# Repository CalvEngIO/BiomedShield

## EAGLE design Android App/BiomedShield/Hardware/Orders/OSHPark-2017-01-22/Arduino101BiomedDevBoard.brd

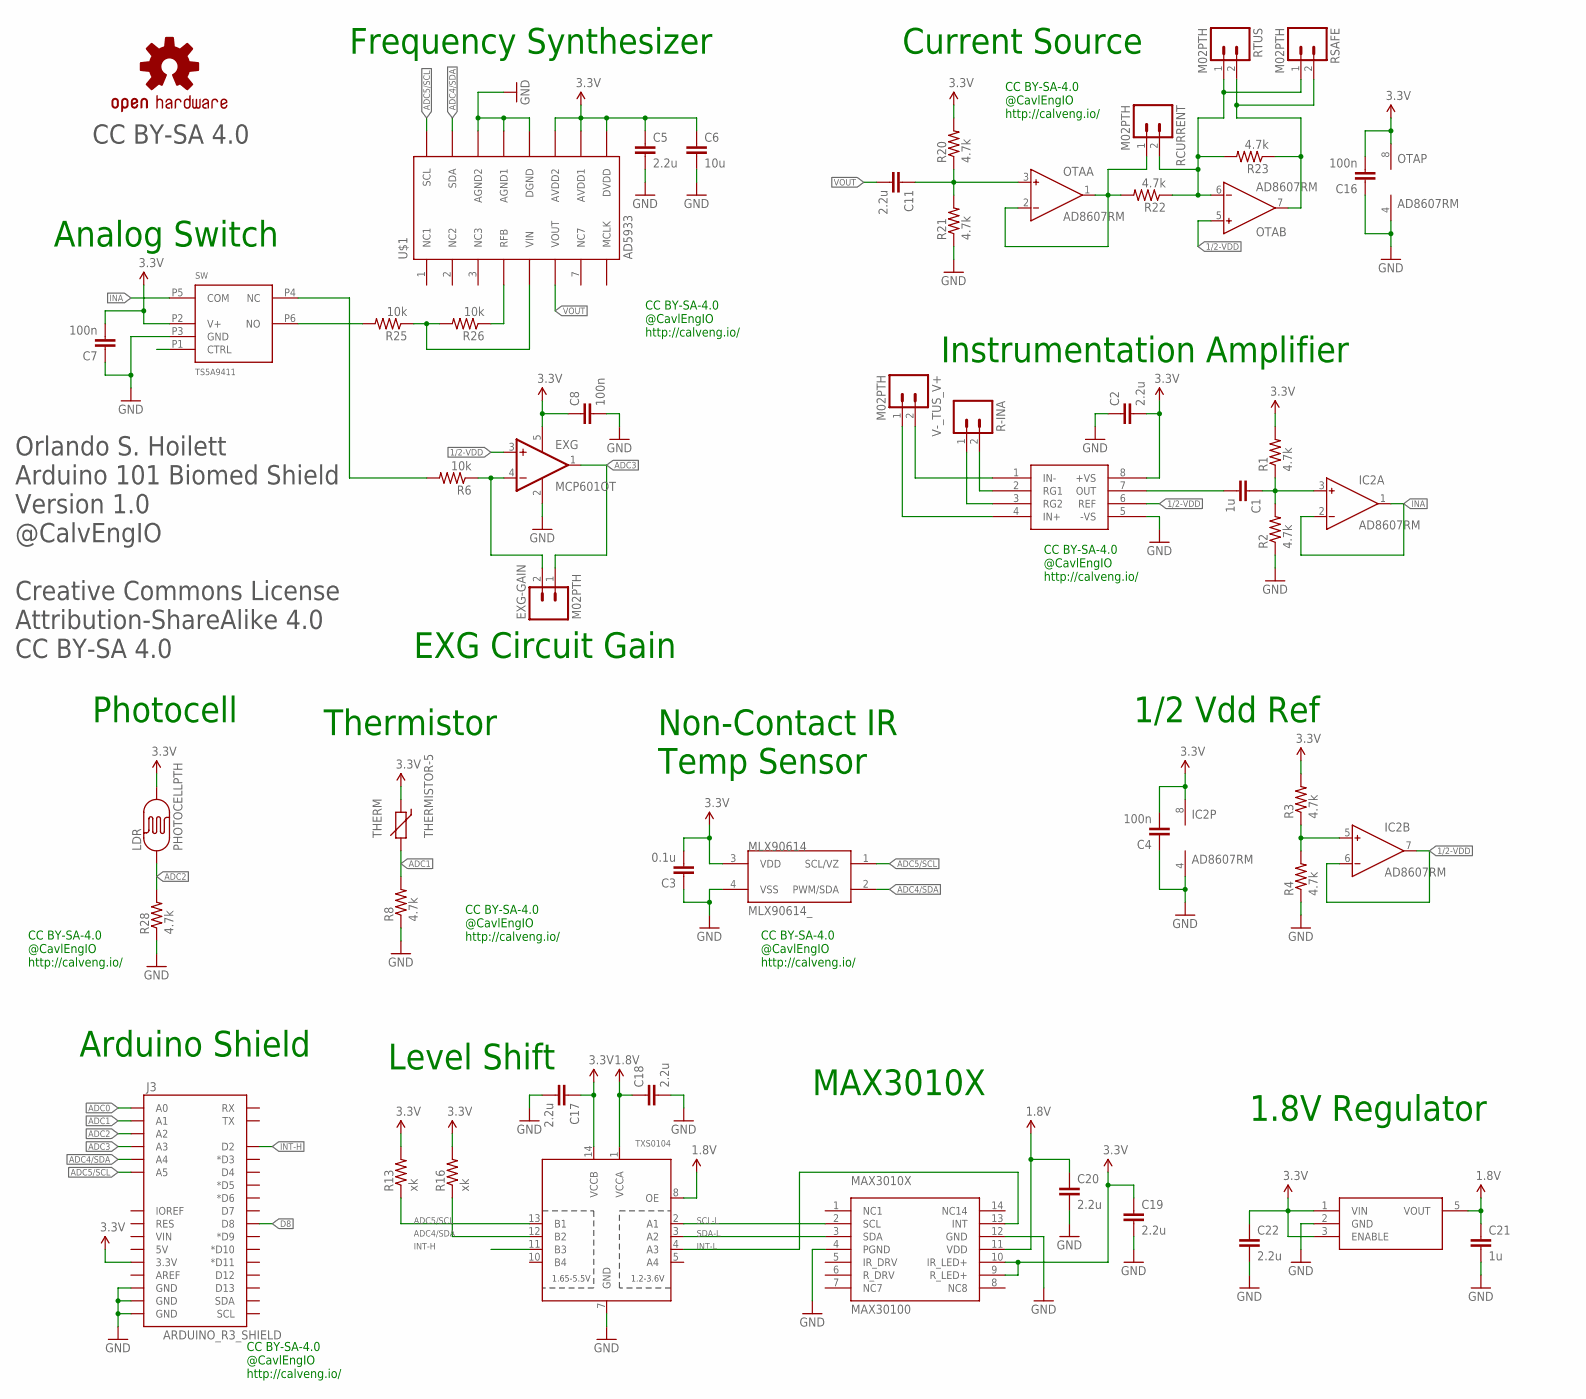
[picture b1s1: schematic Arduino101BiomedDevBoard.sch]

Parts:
1.8V: MIC5504; SOT23-5
C1, C21: 1u; C0402
C2, C5, C11, C17, C18, C19, C20, C22: 2.2u; C0402
C3: 0.1u; C0402
C4, C7, C8, C16: 100n; C0402
C6: 10u; C0805
EXG: MCP601OT; SOT23-5
EXG-GAIN: M02PTH; 1X02
IC2: AD8607RM; MSOP08
INA: AD8220; MSOP08
J3: ARDUINO_R3_SHIELD; UNO_R3_SHIELD
LDR: PHOTOCELLPTH; PHOTOCELL
LOGO3: OSHW-LOGOM; OSHW-LOGO-M
MAX3010X: MAX30100; OESIP14
MLX90614: MLX90614_; TO-39
OTA: AD8607RM; MSOP08
R1, R2, R3, R4, R8, R20, R21, R22, R23, R28: 4.7k; R0402
R6, R25, R26: 10k; R0402
R13, R16: xk; R0402
R-INA: M02PTH; 1X02
RCURRENT: M02PTH; 1X02
RSAFE: M02PTH; 1X02
RTUS: M02PTH; 1X02
SW: TS5A9411; SOT-363
THERM: THERMISTOR-5; R-5
TXS0104: TXB0104PWR; TSSOP14
U$1: AD5933; SSOP-16
V-_TUS_V+: M02PTH; 1X02

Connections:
1.8V: 1.8V.5 (VOUT), C18.1, C20.1, C21.1, MAX3010X.11 (VDD), TXS0104.1 (VCCA), TXS0104.8 (OE)
1/2-VDD: EXG.3 (+IN), IC2.6 (IN-), IC2.7 (OUT), INA.6 (REF), OTA.5 (IN+)
3.3V: 1.8V.1 (VIN), 1.8V.3 (ENABLE), C2.2, C3.2, C4.2, C5.1, C6.1, C7.2, C8.1, C16.2, C17.1, C19.1, C22.1, EXG.5 (V+), IC2.8 (V+), INA.8 (+VS), J3.3.3V, LDR.2, MAX3010X.9 (R_LED+), MAX3010X.10 (IR_LED+), MLX90614.3 (VDD), OTA.8 (V+), R1.2, R3.2, R13.2, R16.2, R20.2, SW.P2 (V+), THERM.1, TXS0104.14 (VCCB), U$1.9 (DVDD), U$1.10 (AVDD1), U$1.11 (AVDD2)
ADC0: J3.A0
ADC1: J3.A1, R8.2, THERM.2
ADC2: J3.A2, LDR.1, R28.2
ADC3: EXG.1 (OUT), EXG-GAIN.1, J3.A3
ADC4/SDA: J3.A4, MLX90614.2 (PWM/SDA), R16.1, TXS0104.12 (B2), U$1.15 (SDA)
ADC5/SCL: J3.A5, MLX90614.1 (SCL/VZ), R13.1, TXS0104.13 (B1), U$1.16 (SCL)
D8: J3.D8, SW.P1 (CTRL)
GND: 1.8V.2 (GND), C2.1, C3.1, C4.1, C5.2, C6.2, C7.1, C8.2, C16.1, C17.2, C18.2, C19.2, C20.2, C21.2, C22.2, EXG.2 (V-), IC2.4 (V-), INA.5 (-VS), J3.GND@0 (GND), J3.GND@1 (GND), J3.GND@2 (GND), MAX3010X.4 (PGND), MAX3010X.12 (GND), MLX90614.4 (VSS), OTA.4 (V-), R2.1, R4.1, R8.1, R21.1, R28.1, SW.P3 (GND), TXS0104.7 (GND), U$1.12 (DGND), U$1.13 (AGND1), U$1.14 (AGND2)
INA: IC2.1 (OUT), IC2.2 (IN-), SW.P5 (COM)
INT-H: J3.D2, TXS0104.11 (B3)
INT-L: MAX3010X.13 (INT), TXS0104.4 (A3)
unnamed: C1.1, IC2.3 (IN+), R1.1, R2.2
unnamed: C1.2, INA.7 (OUT)
unnamed: IC2.5 (IN+), R3.1, R4.2
unnamed: INA.3 (RG2), R-INA.1
unnamed: EXG.4 (-IN), EXG-GAIN.2, R6.1
unnamed: C11.1, OTA.3 (IN+), R20.1, R21.2
unnamed: R25.2, SW.P6 (NO)
unnamed: R25.1, R26.2, U$1.5 (VIN)
unnamed: R6.2, SW.P4 (NC)
unnamed: OTA.1 (OUT), OTA.2 (IN-), R22.2, RCURRENT.1
unnamed: OTA.6 (IN-), R22.1, R23.2, RCURRENT.2, RSAFE.1, RTUS.1
unnamed: OTA.7 (OUT), R23.1, RSAFE.2, RTUS.2
unnamed: INA.1 (IN-), V-_TUS_V+.2
unnamed: INA.4 (IN+), V-_TUS_V+.1
unnamed: INA.2 (RG1), R-INA.2
unnamed: R26.1, U$1.4 (RFB)
SCL-L: MAX3010X.2 (SCL), TXS0104.2 (A1)
SDA-L: MAX3010X.3 (SDA), TXS0104.3 (A2)
VOUT: C11.2, U$1.6 (VOUT)

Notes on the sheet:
Orlando S. Hoilett Arduino 101 Biomed Shield Version 1.0 @CalvEngIO Creative Commons License Attribution-ShareAlike 4.0 CC BY-SA 4.0
Level Shift
MAX3010X
1.8V Regulator
Non-Contact IR Temp Sensor
Current Source
Instrumentation Amplifier
Frequency Synthesizer
1/2 Vdd Ref
Photocell
Arduino Shield
Thermistor
EXG Circuit Gain
Analog Switch
CC BY-SA 4.0
CC BY-SA-4.0 @CavlEngIO http://calveng.io/

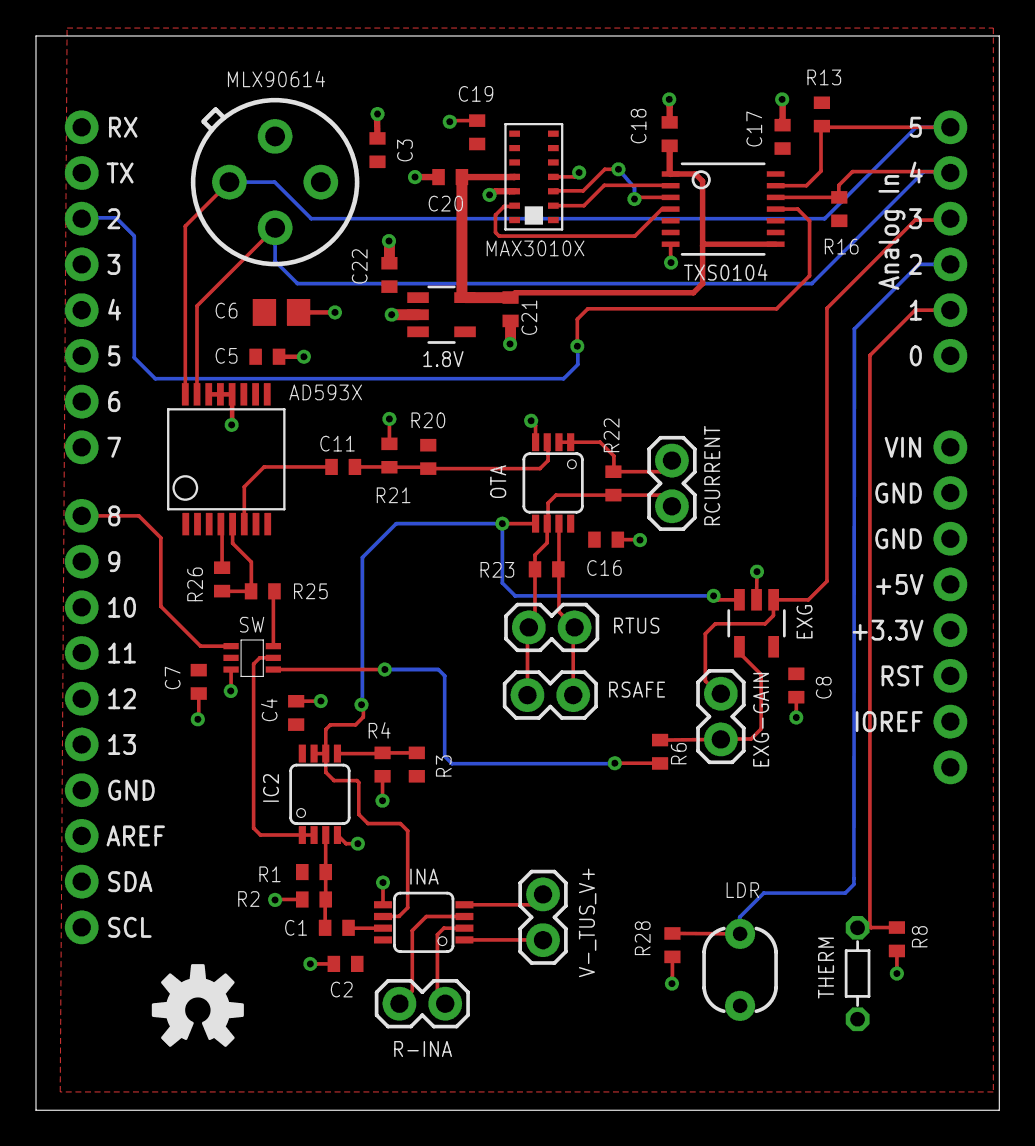
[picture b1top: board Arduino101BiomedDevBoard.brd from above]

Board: 2 copper layers, 53.5 x 59.7 mm, 51 parts (0 on the bottom side), 32 nets.

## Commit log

2017-03-27 initial commit. Still lot of work to do
2017-06-20 bare bones for the arduino library
2017-06-23 Added info on UV sensor
2017-07-13 Added interrupt functionality
2017-07-17 Changed Function Names
2017-07-17 Added functions
2017-07-22 Added UV Index Lookup

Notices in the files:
parts and their libraries:
SparkFun-Aesthetics: Licensing: CC v3.0 Share-Alike You are welcome to use this library for commercial purposes.
SparkFun-Sensors: Licensing: Creative Commons ShareAlike 4.0 International - https://creativecommons.org/licenses/by-sa/4.0
